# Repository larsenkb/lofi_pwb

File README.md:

# lofi window/door sensor

## Uses attiny84a + nrf24l01p + tpl5111 to achieve very low power.

This project was influenced by a LoFi board designed by
David Cook and entered in a hackaday contest.
See https://hackaday.io/project/1552-lofi

At the beginning, I used OshPark to make some of his
boards and hacked them to work with an NRF24l01+.

I have mated the lofi board with a nrf24l01+ instead of using
the 433 MHz transmitter described at the above link.

I'm using the nrf24 in its very basic form, using minimal
features.

I am using parts of xprintf.[ch] by ChaN (see xprintf.c for copyright)
I am using parts of nrf24.[ch] by <ihsan@ehribar.me>
(see nrf24.c for license)

The lofi+nrf24 combo draws ~2 uA in the idle mode.
It can monitor one reed switch, Vcc and internal temperature.
It uses the internal RC oscillator so timing is not very accurate.
The switch can be configured to generate an interrupt on Pin Change
which will trigger a transmission. Otherwise, it is only polled
and switch state will be transmitted at the polling frequency.
The polling period is configured in eeprom, to be a multiple
of the TPL5111 period.

The LDO can be installed if you want to power lofi from a voltage > 3.3V. Otherwise, just solder a jumper across the Vin to Vout of the LDO.

Resistors R1, R2, and R3 are in parallel-series so you can get a precise timing resistance with less precise resistors.

I use a SPDT reed switch so that I do not need a pull-up or pull-down resistor, thus reducing power further.

A 10-bit incrementing count can also be enabled and will be
sent at a frequency determined by eeprom and TPL5111.

I am making my own board now that uses a TPL5111 to periodically
wake the ATtiny84. I do not power down the t84 but instead,
use a Pin Change function to monitor the TPL5111 DRVn pin.
So, I continuously draw about 2uA.
I chose this method, so that my original code did not have
to change much. I can still use SRAM between sleeps.
If I powered down the t84 between DRVn assertions, I would
have to send all messages each time. I don't think there
would be a method of only sending Vcc messages every n
DRV assertions.

I'm using spin loop delays. See util/delay basic.h.  delay_loop_1 loop is three cycles and takes an 8-bit loop counter. 3us * 256 is max delay.  delay_loop_2 loop is four cycles and takes a 16-bit loop counter. 4us * 65536 is max delay.

Configuration is stored in the eeprom starting at addr 0.
See config_t structure for details.

---

The front view of lofi looks like this:

The back view of lofi looks like this:

The folded view of lofi looks like this:

I used a clothes pin to make my programmer:

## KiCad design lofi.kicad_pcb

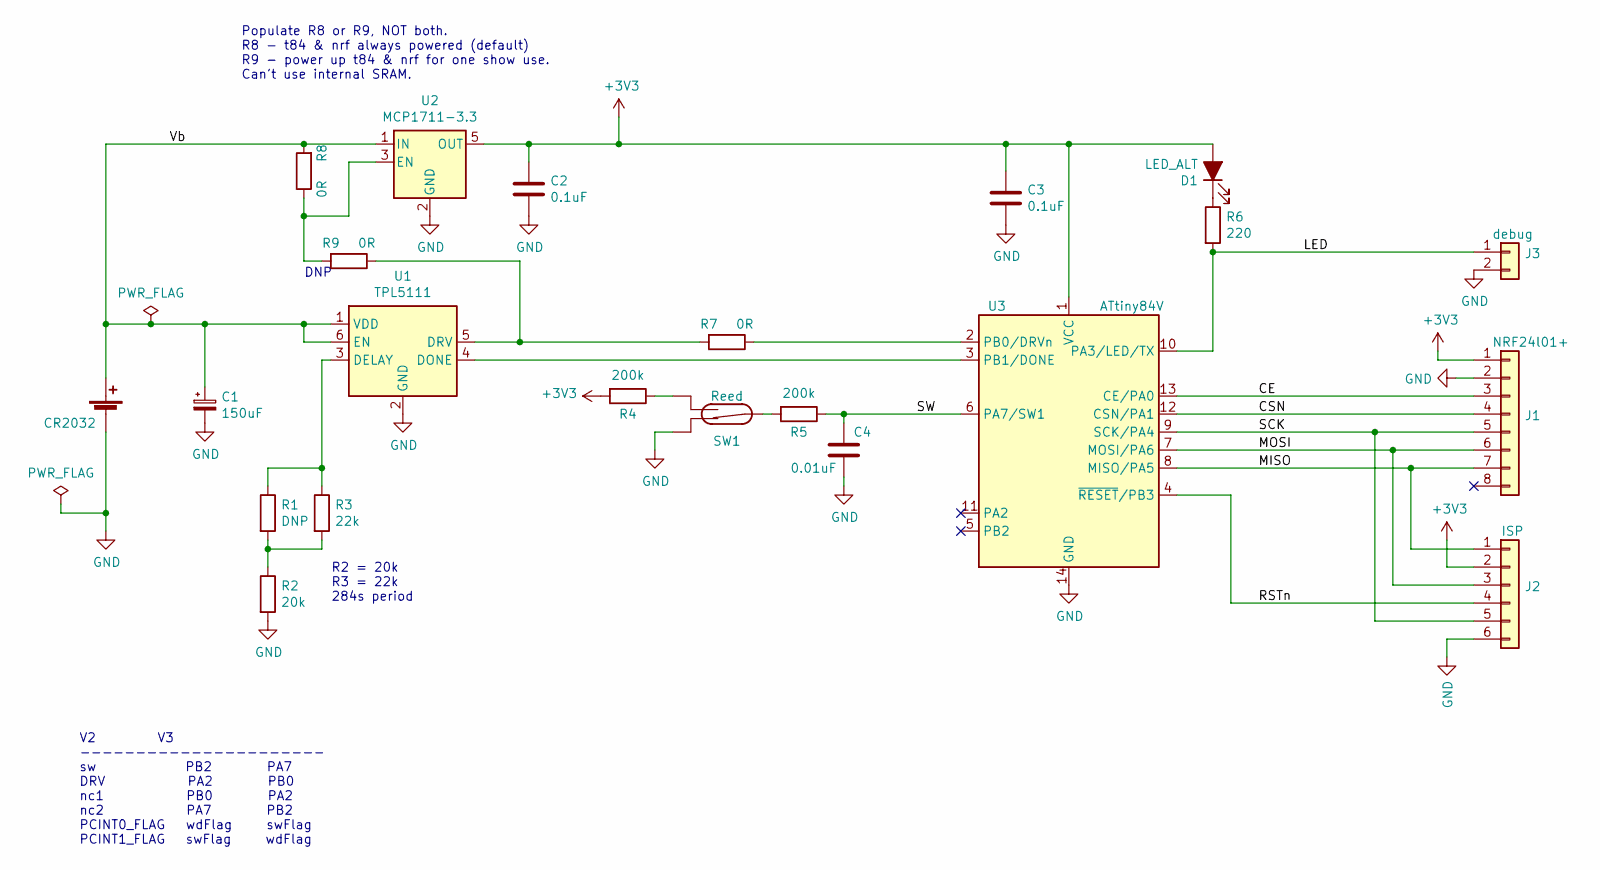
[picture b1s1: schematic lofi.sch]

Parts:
BT1: CR2032; CR2032_battery_clip
C1: 150uF; C_2816_7142Metric_Pad3.20x4.45mm_HandSolder
C2, C3: 0.1uF; C_0805_2012Metric_Pad1.15x1.40mm_HandSolder
C4: 0.01uF; C_0805_2012Metric_Pad1.15x1.40mm_HandSolder
D1: LED_ALT; D_0805_2012Metric_Pad1.15x1.40mm_HandSolder
J1: NRF24l01+; nrf24l01p
J2: ISP
J3: debug; R_0805_2012Metric_Pad1.15x1.40mm_HandSolder
R1: DNP; R_0805_2012Metric_Pad1.15x1.40mm_HandSolder
R2: 20k; R_0805_2012Metric_Pad1.15x1.40mm_HandSolder
R3: 22k; R_0805_2012Metric_Pad1.15x1.40mm_HandSolder
R4, R5: 200k; R_0805_2012Metric_Pad1.15x1.40mm_HandSolder
R6: 220; R_0805_2012Metric_Pad1.15x1.40mm_HandSolder
R7: 0R; R_0805_2012Metric_Pad1.15x1.40mm_HandSolder
R8, R9: 0R; R_0805_2012Metric_Pad1.20x1.40mm_HandSolder
SW1: Reed; REED_SPDT
U1: TPL5111
U2: MCP1711-3.3; MCP1711
U3: ATtiny84V; SOIC-14

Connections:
+3V3: C2.1, C3.1, D1.2 (A), J1.1, J2.2, R4.2, U2.5 (OUT), U3.1 (VCC)
/CE: J1.3, U3.13 (CE/PA0)
/CSN: J1.4, U3.12 (CSN/PA1)
/LED: J3.1, R6.2, U3.10 (PA3/LED/TX)
/MISO: J1.7, J2.1, U3.8 (MISO/PA5)
/MOSI: J1.6, J2.3, U3.7 (MOSI/PA6)
/RSTn: J2.4, U3.4 (~RESET~/PB3)
/SCK: J1.5, J2.5, U3.9 (SCK/PA4)
/SW: C4.1, R5.1, U3.6 (PA7/SW1)
/Vb: BT1.1 (+), C1.1, R8.2, U1.1 (VDD), U1.6 (EN), U2.1 (IN)
GND: BT1.2 (-), C1.2, C2.2, C3.2, C4.2, J1.2, J2.6, J3.2, R2.2, SW1.1, U1.2 (GND), U2.2 (GND), U3.14 (GND)
unnamed: D1.1 (K), R6.1
unnamed: R1.1, R3.1, U1.3 (DELAY)
unnamed: R1.2, R2.1, R3.2
unnamed: R4.1, SW1.3
unnamed: R5.2, SW1.2
unnamed: R7.1, U3.2 (PB0/DRVn)
unnamed: R7.2, R9.1, U1.5 (DRV)
unnamed: R8.1, R9.2, U2.3 (EN)
unnamed: U1.4 (DONE), U3.3 (PB1/DONE)

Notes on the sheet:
DNP
Populate R8 or R9, NOT both. R8 - t84 & nrf always powered (default) R9 - power up t84 & nrf for one show use. Can't use internal SRAM.
V2 V3 ---------------------- sw PB2 PA7 DRV PA2 PB0 nc1 PB0 PA2 nc2 PA7 PB2 PCINT0_FLAG wdFlag swFlag PCINT1_FLAG swFlag wdFlag
R2 = 20k R3 = 22k 284s period

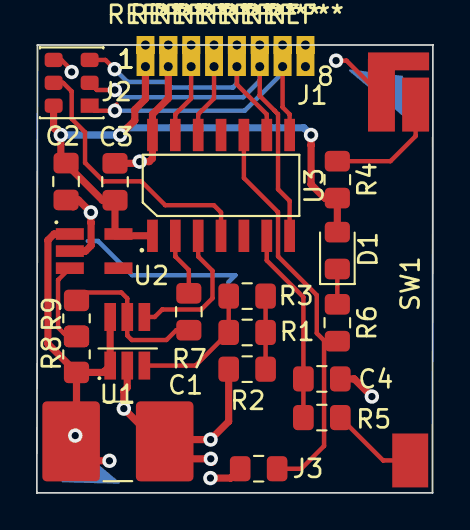
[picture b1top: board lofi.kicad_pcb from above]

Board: 2 copper layers, 22.0 x 24.9 mm, 22 parts (1 on the bottom side), 20 nets.

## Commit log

2019-08-16 initial checkin
2019-08-16 changed SOIC-14 footprint
2019-08-17 as sent to OSHPark
2019-08-17 really, this time, as sent to OSHPark
2020-02-06 version 0.2 and 0.3
2020-02-06 added zips
2020-02-06 added to README.md
2020-02-06 fixing README.md
2020-02-06 added some images
2021-05-01 latest pwb version is 0.4
2021-05-01 removed zipped files
